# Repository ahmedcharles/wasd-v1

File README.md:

# WASD v1 Keyboard to iCEBreaker Bitsy Bridge

## License

```
   Copyright 2022 Ahmed Charles <me@ahmedcharles.com>

   This work is licensed under a Creative Commons
   Attribution-ShareAlike 4.0 International License.
   To view a copy of this license, visit

       http://creativecommons.org/licenses/by-sa/4.0/
```

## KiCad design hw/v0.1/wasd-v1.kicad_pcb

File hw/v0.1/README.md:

# WASD v1 Keyboard to iCEBreaker Bitsy Bridge - v0.1

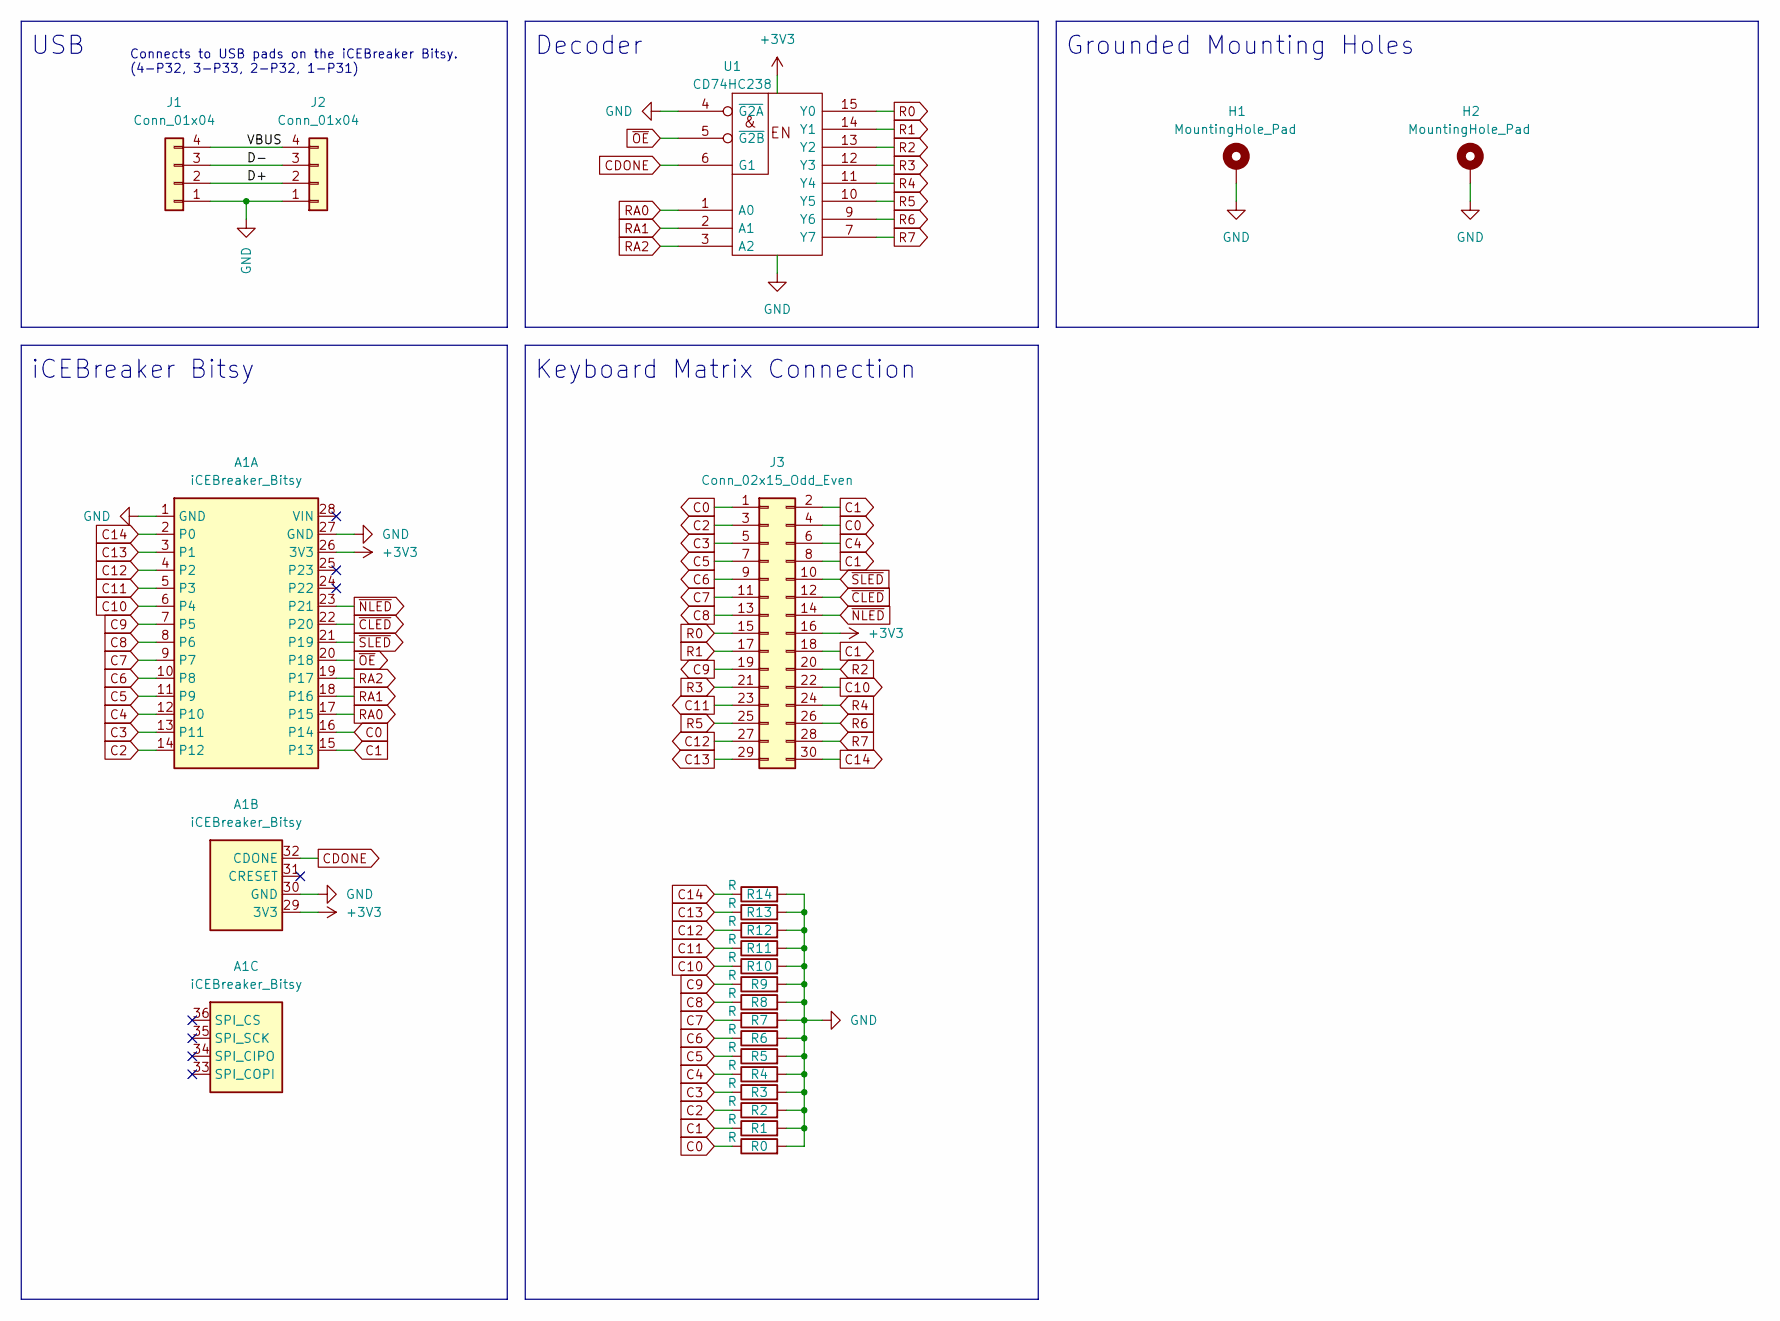
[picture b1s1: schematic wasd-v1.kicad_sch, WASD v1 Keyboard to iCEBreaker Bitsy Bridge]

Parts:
A1: iCEBreaker_Bitsy; iCEBreaker_Bitsy_RM
H1, H2: MountingHole_Pad; MountingHole_2.5mm_Pad
J1: Conn_01x04; JST_PH_S4B-PH-K_1x04_P2.00mm_Horizontal
J2: Conn_01x04; PinHeader_1x04_P2.54mm_Vertical
J3: Conn_02x15_Odd_Even; PinHeader_2x15_P2.00mm_Vertical
R0, R1, R2, R3, R4, R5, R6, R7, R8, R9, R10, R11, R12, R13, R14: R; R_Axial_DIN0207_L6.3mm_D2.5mm_P10.16mm_Horizontal
U1: CD74HC238; DIP-16_W7.62mm

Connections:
+3V3: A1.26 (3V3), A1.29 (3V3), J3.16, U1.16 (VCC)
/D+: J1.2, J2.2
/D-: J1.3, J2.3
/VBUS: J1.4, J2.4
C0: A1.16 (P14), J3.1, J3.4, R0.1
C1: A1.15 (P13), J3.2, J3.8, J3.18, R1.1
C2: A1.14 (P12), J3.3, R2.1
C3: A1.13 (P11), J3.5, R3.1
C4: A1.12 (P10), J3.6, R4.1
C5: A1.11 (P9), J3.7, R5.1
C6: A1.10 (P8), J3.9, R6.1
C7: A1.9 (P7), J3.11, R7.1
C8: A1.8 (P6), J3.13, R8.1
C9: A1.7 (P5), J3.19, R9.1
C10: A1.6 (P4), J3.22, R10.1
C11: A1.5 (P3), J3.23, R11.1
C12: A1.4 (P2), J3.27, R12.1
C13: A1.3 (P1), J3.29, R13.1
C14: A1.2 (P0), J3.30, R14.1
CDONE: A1.32 (CDONE), U1.6 (G1)
GND: A1.1 (GND), A1.27 (GND), A1.30 (GND), H1.1, H2.1, J1.1, J2.1, R0.2, R1.2, R2.2, R3.2, R4.2, R5.2, R6.2, R7.2, R8.2, R9.2, R10.2, R11.2, R12.2, R13.2, R14.2, U1.4 (~G2A), U1.8 (GND)
R0: J3.15, U1.15 (Y0)
R1: J3.17, U1.14 (Y1)
R2: J3.20, U1.13 (Y2)
R3: J3.21, U1.12 (Y3)
R4: J3.24, U1.11 (Y4)
R5: J3.25, U1.10 (Y5)
R6: J3.26, U1.9 (Y6)
R7: J3.28, U1.7 (Y7)
RA0: A1.17 (P15), U1.1 (A0)
RA1: A1.18 (P16), U1.2 (A1)
RA2: A1.19 (P17), U1.3 (A2)
~CLED: A1.22 (P20), J3.12
~NLED: A1.23 (P21), J3.14
~OE: A1.20 (P18), U1.5 (~G2B)
~SLED: A1.21 (P19), J3.10

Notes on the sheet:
Grounded Mounting Holes
Decoder
USB
Keyboard Matrix Connection
Connects to USB pads on the iCEBreaker Bitsy. (4-P32, 3-P33, 2-P32, 1-P31)
iCEBreaker Bitsy

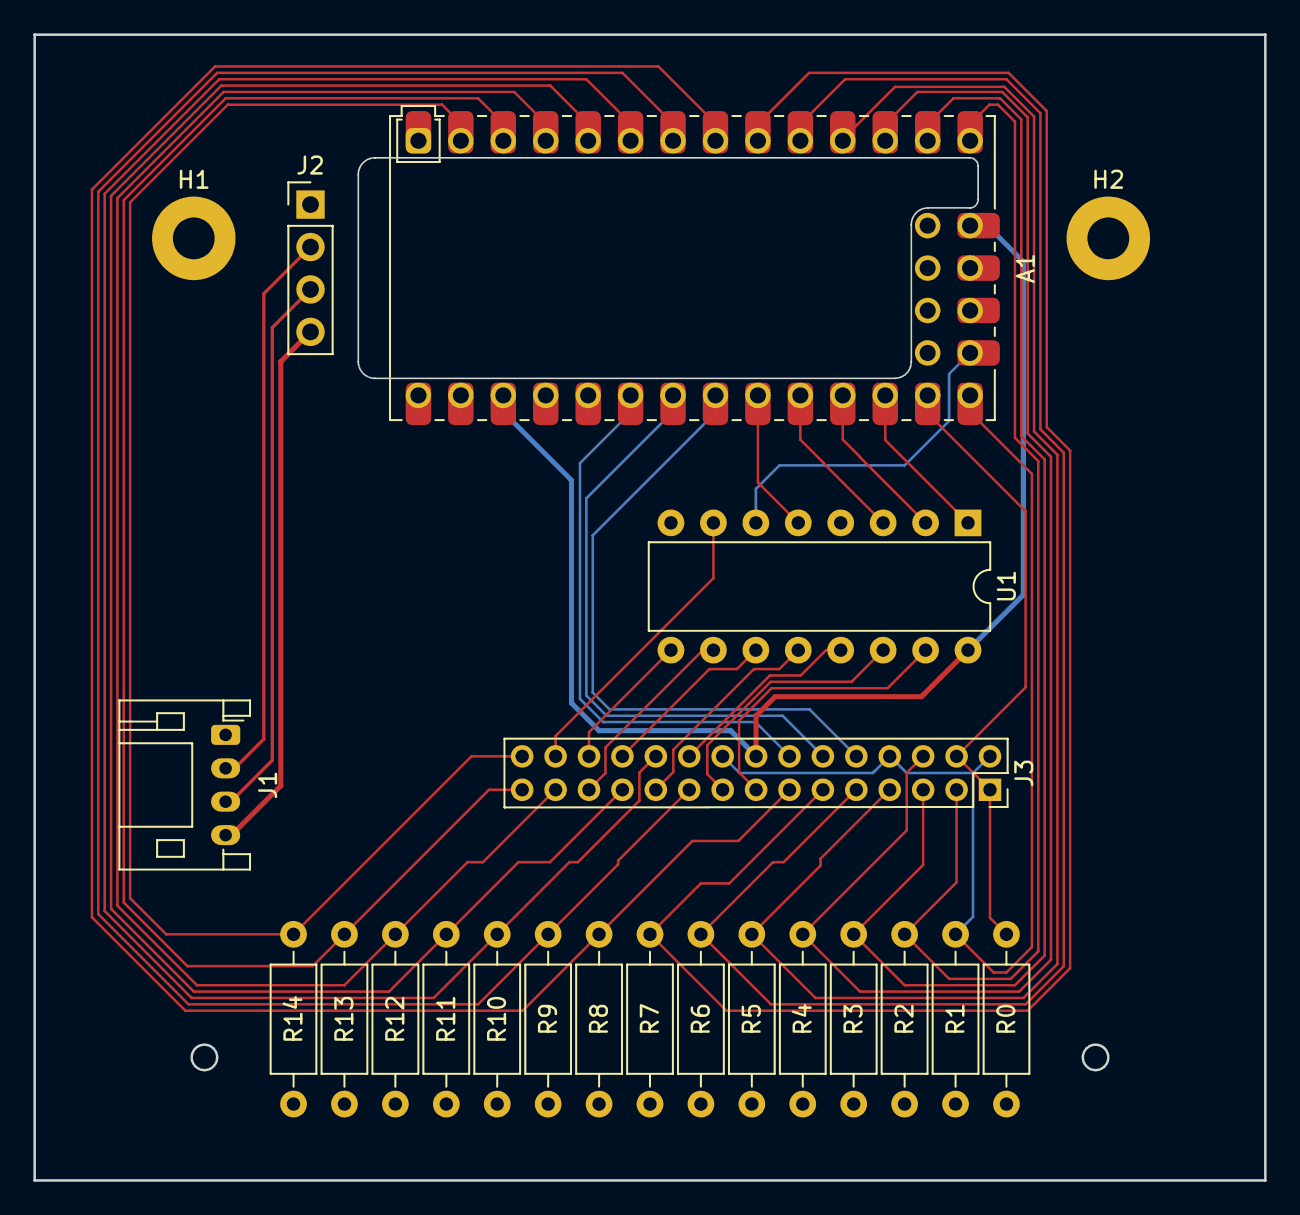
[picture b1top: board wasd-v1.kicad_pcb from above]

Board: 2 copper layers, 73.7 x 68.6 mm, 22 parts (0 on the bottom side), 36 nets.

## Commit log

2022-02-20 Initial empty commit.
2022-02-21 Add initial files.
2022-03-03 WASD v1 Keyboard to iCEBreaker Bitsy Bridge
